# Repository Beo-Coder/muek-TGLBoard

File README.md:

# TGL Board

### 8x16 ARGB LED Board

This project is a small low profile PCB LED matrix that can be used as a name tag
or to display various text and animations and to play games.

If you have your own "programmable" version,
you can read more about programming [here](#programming)

# About
This project was initially planned as a gift for teachers after our graduation.  
It is a small and low cost LED matrix board.  
It consists of a 8x16 ARGB LED matrix, two buttons as user input and a USB-C jack for powering and programming. 
On the front and backside there are several places where custom text can be written to,
to further individualize the board.  
One of the main goals was that the whole board is visually appealing
and can be used without an enclosure to have a simpler and sleeker looking product.

The electronics consist of an RP2040 microcontroller and a 2 MB (16 Mbit) flash IC.  
You can read more about the electronic [here](#hardware)

To program the board,
you can use SWD on the Tag-Connect connector on the backside as well as on the [custom pads on the backside](#swd-interface).  
It is also possible to program the board over USB-C,
but this needs further hardware modifications (Read more about [here](#usb-c))

# Software
Currently, the software has four modes:

- Displaying text
- Showing animations
- Playing a game
- Setting the brightness

Between these modes, you can easily switch by holding down both buttons at the same time and waiting a bit.
You can choose the mode by going left or right and select it by either waiting or pressing both buttons again.

Inside the different modes, the two buttons have different meanings.
They change the text, the color of the text, the animation, or you can play the game.

## Text
The text can be individually programmed by modifying the [board_text_config.h](src/DisplayText/board_text_config.h) file.

## Animations
There are currently seven different animations:

- Fireworks
- Snake "AI"
- Conway's Game of Life
- Meteorite rain
- Smooth rainbow
- 'Hard' rainbow
- Jumping 'thing'

## Games
There are also two games, but only one is selected by default.

- Dino Game (Default)
- Tetris

To change the game, you need to modify [main.cpp](src/main.cpp).

### Controls: 
#### Dino Game: 
**Left**: *Duck*  
**Right**: *Jump*

After each game, your score and your high score is shown.

#### Tetris:
**Left**: *Moves block to the left*  
**Right**: *Moves block to the right*  
**Right while holding left**: *Rotating block*

After each game, your score and your high score is shown.  
This Tetris game was created by @StarMiner99

## Brightness control
The brightness is only saved when you switch the menu after setting the desired brightness.

# Programming
You can either use PlatformIO (Arduino Framework) or the official C/C++ SDK from Raspberry Pi.  
If you want to use the C/C++ SDK, please use the c-SDK branch.

For details on how these two differ, read [Runtime](README_runtime.md).

## Usage

You need PlatformIO to use this project.  
Arduino IDE might work too (not tested).

In the platform.ini file, there are now two build environments.
`pico_normal` and `pico_fast` you can read about the differences here [Runtime](README_runtime.md).  

For your own programming, you can use my pioMatrixOutput library.
Documentation is here [pioMatrixOutput](READMEpioMatrixOutput.md).

For your own text, you can use my library.
Documentation is here [Textcontroller](README_textController.md).

For flash usage, read here [Flash](README_flash.md).

**Important:**
If you brick your board (can't upload anything) please read [here](README_bricked.md).  

# Hardware

Schematic, layout, BOM and gerber files can be found [here](hardware).  

Each button has a 10k-ohm pull-down resistor and a 100-nF capacitor for debouncing.  

The design of the MCU section follows more or less the [hardware design guide for the RP2040](https://datasheets.raspberrypi.com/rp2040/hardware-design-with-rp2040.pdf).

Because of the design,
it was not possible to add a 100-nF capacitor to each LED, but each row of LEDs (16 each) has its own 10-uF cap
(I know it is not perfect or a replacement).  
Also,
there are multiple more capacitors to further decouple the matrix as good as possible
so that fast-changing patterns do not affect the MCU and its operations.  
This is further improved by the fact the whole MCU subsystem runs on 3.3V over a LDO and not the 5.0V that the LEDs run on. 
While testing, I haven't had any issues with noisy power lines.  
Also, when measuring with my oscilloscope and the matrix turning fully on and fully off as fast as possible, 
I couldn't measure any serious noise on the 5.0V rail nor on the 3.3V rail for the MCU.

## USB-C
Behind the USB-C jack, there are two unpopulated pads.
These pads cut the USB data signal, so that you can't program the board over USB.  
This can be useful, for example,
if you do not want that your teachers get confused when they plug it in to their pc :^)  
If you want to enable USB programming,
you need to short these two pads either with an 0402 0-ohm resistor or simply with solder bridges.  
Be aware that this is quite challenging to solder, you shouldn't destroy/desolder neighboring components.  
Maybe it is easier if you use a hotplate and 0-ohm resistors (Haven't tried it).  
If you order new boards, you can add those to be assembled too.  
The 27-ohm resistors on each USB data line necessary for the RP2040 are already assembled.

It should look something like this:

## SWD interface
The three unnamed pads on the backside above the UART pads are connections for SWD programming. 

Pinout:
<pre>
board outline
 |
 |          +---+            +---+           +---+
 |         /     \          /     \         /     \
 |        /       \        /       \       /       \
 |       +   RUN   +      +   SWD   +     +  SWCLK  +
 |        \       /        \       /       \       /
 |         \     /          \     /         \     /
 |          +---+            +---+           +---+
 |
 |                  +---+            +---+          
 |                 /     \          /     \ 
 |                /       \        /       \
 |               +   Tx    +      +   Rx    +
 |                \       /        \       /       
 |                 \     /          \     /   
 |                  +---+            +---+
</pre>

# Stand
I also created a stand for the board.
It has three different angles: 90°, 70° and 60°.  
It has place for a name on the top side and for text on the bottom side.  
Inside the stand there are three slots for 1 cent coins (EU) to make the stand more stable.  
If you want to insert those coins, you need to stop the print mid-way and insert/glue the coins in place.  
3mf and STL files can be found [here](hardware/Stand)

If you have any questions, please contact me.

© 2024 Leonhard Baschang

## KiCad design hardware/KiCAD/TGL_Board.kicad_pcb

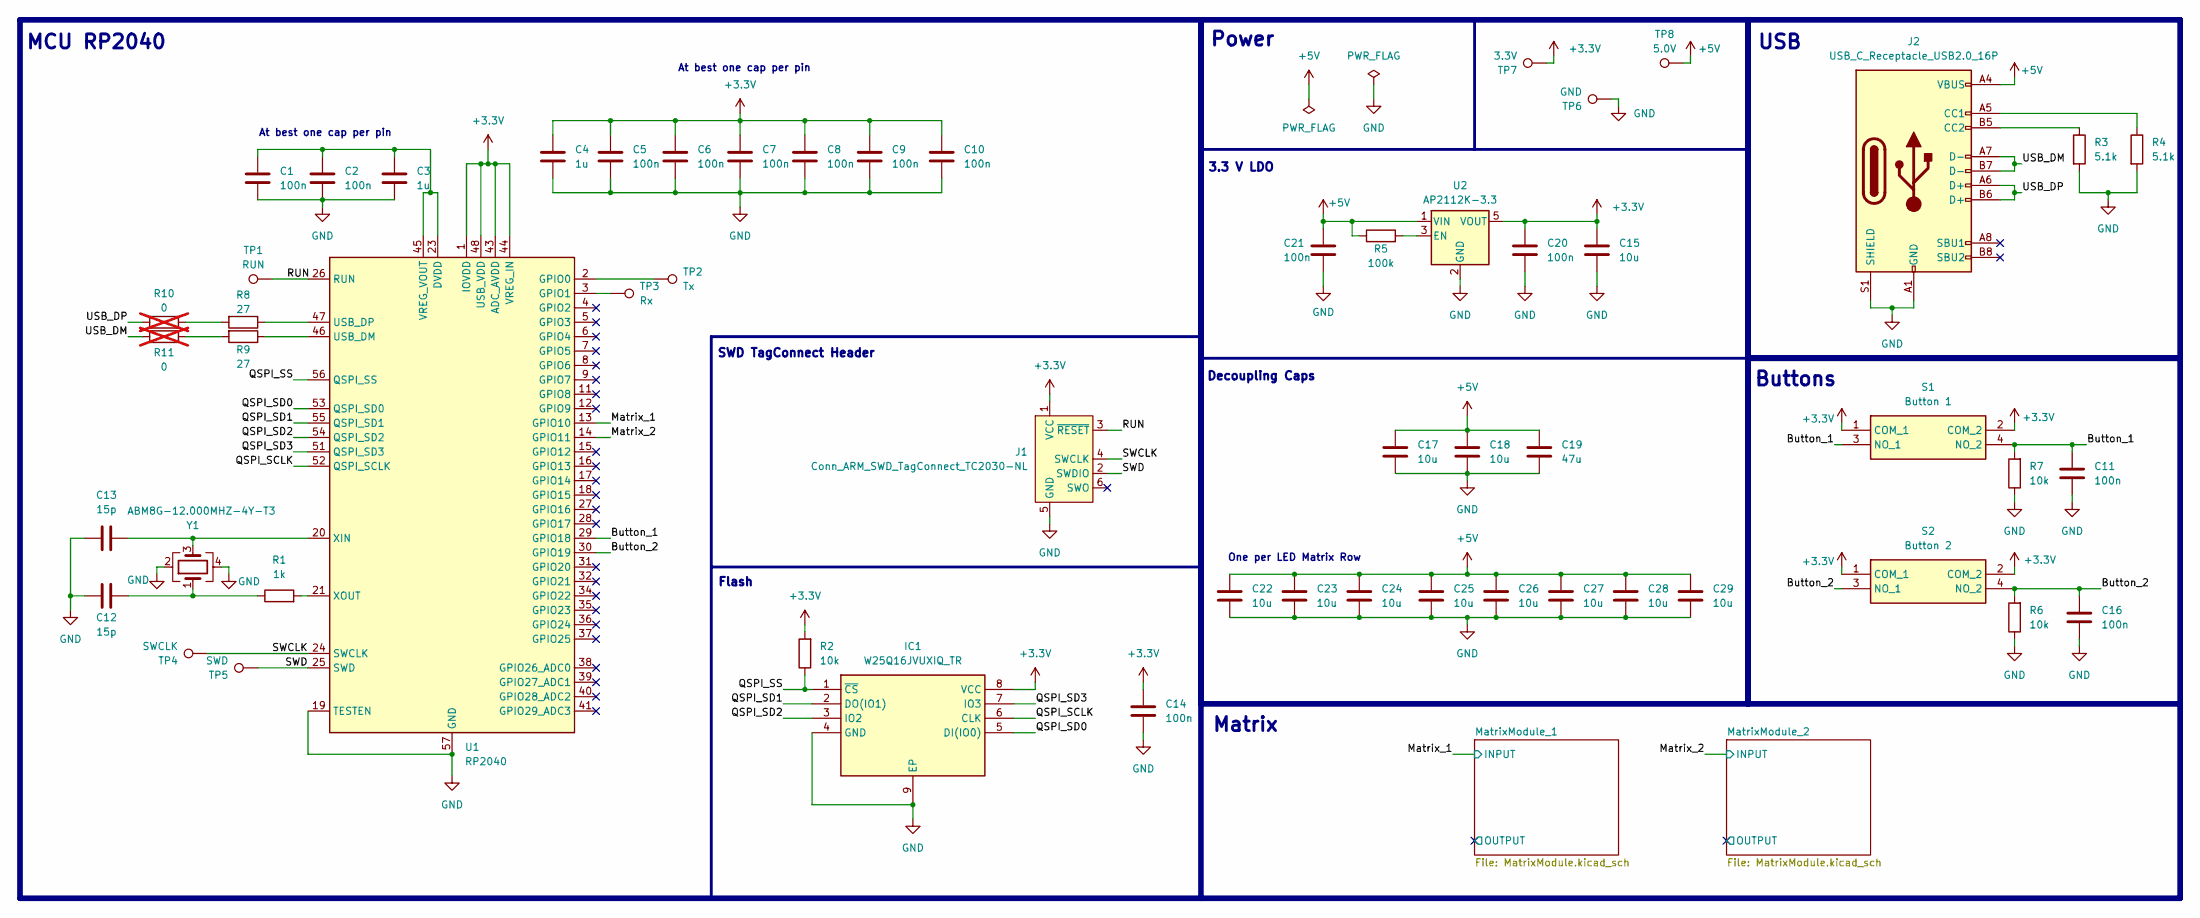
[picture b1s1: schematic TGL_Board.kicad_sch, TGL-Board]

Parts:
C1, C2, C5, C6, C7, C8, C9, C10, C11, C14, C16, C20, C21: 100n; C_0402_1005Metric; LCSC C1525
C3, C4: 1u; C_0402_1005Metric; LCSC C52923
C12, C13: 15p; C_0402_1005Metric; LCSC C1548
C15, C17, C18, C22, C23, C24, C25, C26, C27, C28, C29: 10u; C_0603_1608Metric; LCSC C19702
C19: 47u; C_0805_2012Metric; LCSC C16780
IC1: W25Q16JVUXIQ_TR; SON50P300X200X60-9L; Mouser Part Number 454-W25Q16JVUXIQTR
J1: Conn_ARM_SWD_TagConnect_TC2030-NL; Tag-Connect_TC2030-IDC-NL_2x03_P1.27mm_Vertical
J2: USB_C_Receptacle_USB2.0_16P; USB_C_Receptacle_GCT_USB4105-xx-A_16P_TopMnt_Horizontal; LCSC C2858270
R1: 1k; R_0402_1005Metric; LCSC C11702
R2, R6, R7: 10k; R_0402_1005Metric; LCSC C25744
R3, R4: 5.1k; R_0402_1005Metric; LCSC C25905
R5: 100k; R_0402_1005Metric; LCSC C25741
R8, R9: 27; R_0402_1005Metric; LCSC C25156
R10, R11: 0; R_0402_1005Metric; not fitted
S1: Button 1; PTS526SK15SMTR2LFS; Mouser Part Number 611-PTS526SK15SMR2L
S2: Button 2; PTS526SK15SMTR2LFS; Mouser Part Number 611-PTS526SK15SMR2L
TP1: RUN; TestPoint_Pad_D1.0mm
TP2: Tx; TestPoint_Pad_D1.0mm
TP3: Rx; TestPoint_Pad_D1.0mm
TP4: SWCLK; TestPoint_Pad_D1.0mm
TP5: SWD; TestPoint_Pad_D1.0mm
TP6: GND; TestPoint_Pad_D1.0mm
TP7: 3.3V; TestPoint_Pad_D1.0mm
TP8: 5.0V; TestPoint_Pad_D1.0mm
U1: RP2040; QFN-56-1EP_7x7mm_P0.4mm_EP3.2x3.2mm; LCSC C2040
U2: AP2112K-3.3; SOT-23-5; LCSC C51118
Y1: ABM8G-12.000MHZ-4Y-T3; Crystal_SMD_3225-4Pin_3.2x2.5mm; LCSC C9002

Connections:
+3.3V: C4.1, C5.2, C6.2, C7.2, C8.2, C9.2, C10.2, C14.1, C15.2, C20.2, IC1.8 (VCC), J1.1 (VCC), R2.2, S1.1 (COM_1), S1.2 (COM_2), S2.1 (COM_1), S2.2 (COM_2), TP7.1, U1.1 (IOVDD), U1.10 (IOVDD), U1.22 (IOVDD), U1.33 (IOVDD), U1.42 (IOVDD), U1.43 (ADC_AVDD), U1.44 (VREG_IN), U1.48 (USB_VDD), U1.49 (IOVDD), U2.5 (VOUT)
+5V: C17.2, C18.2, C19.2, C21.1, C22.2, C23.2, C24.2, C25.2, C26.2, C27.2, C28.2, C29.2, J2.A4 (VBUS), J2.A9 (VBUS), J2.B4 (VBUS), J2.B9 (VBUS), R5.1, TP8.1, U2.1 (VIN); also elsewhere on the board
/Button_1: C11.2, R7.2, S1.3 (NO_1), S1.4 (NO_2), U1.29 (GPIO18)
/Button_2: C16.2, R6.2, S2.3 (NO_1), S2.4 (NO_2), U1.30 (GPIO19)
/Matrix_1: U1.13 (GPIO10); also elsewhere on the board
/Matrix_2: U1.14 (GPIO11); also elsewhere on the board
/QSPI_SCLK: IC1.6 (CLK), U1.52 (QSPI_SCLK)
/QSPI_SD0: IC1.5 (DI(IO0)), U1.53 (QSPI_SD0)
/QSPI_SD1: IC1.2 (DO(IO1)), U1.55 (QSPI_SD1)
/QSPI_SD2: IC1.3 (IO2), U1.54 (QSPI_SD2)
/QSPI_SD3: IC1.7 (IO3), U1.51 (QSPI_SD3)
/QSPI_SS: IC1.1 (~CS), R2.1, U1.56 (QSPI_SS)
/RUN: J1.3 (~RESET), TP1.1, U1.26 (RUN)
/SWCLK: J1.4 (SWCLK), TP4.1, U1.24 (SWCLK)
/SWD: J1.2 (SWDIO), TP5.1, U1.25 (SWD)
/USB_DM: J2.A7 (D-), J2.B7 (D-), R11.2
/USB_DP: J2.A6 (D+), J2.B6 (D+), R10.2
GND: C1.1, C2.1, C3.1, C4.2, C5.1, C6.1, C7.1, C8.1, C9.1, C10.1, C11.1, C12.2, C13.2, C14.2, C15.1, C16.1, C17.1, C18.1, C19.1, C20.1, C21.2, C22.1, C23.1, C24.1, C25.1, C26.1, C27.1, C28.1, C29.1, IC1.4 (GND), IC1.9 (EP), J1.5 (GND), J2.A1 (GND), J2.A12 (GND), J2.B1 (GND), J2.B12 (GND), J2.S1 (SHIELD), R3.2, R4.2, R6.1, R7.1, TP6.1, U1.19 (TESTEN), U1.57 (GND), U2.2 (GND), Y1.2, Y1.4; also elsewhere on the board
unnamed: C12.1, R1.1, Y1.1
unnamed: J2.A5 (CC1), R4.1
unnamed: J2.B5 (CC2), R3.1
unnamed: R8.2, R10.1
unnamed: R9.2, R11.1
unnamed: TP2.1, U1.2 (GPIO0)
unnamed: TP3.1, U1.3 (GPIO1)
unnamed: R9.1, U1.46 (USB_DM)
unnamed: R8.1, U1.47 (USB_DP)
unnamed: C1.2, C2.2, C3.2, U1.23 (DVDD), U1.45 (VREG_VOUT), U1.50 (DVDD)
unnamed: C13.1, U1.20 (XIN), Y1.3
unnamed: R1.2, U1.21 (XOUT)
unnamed: R5.2, U2.3 (EN)

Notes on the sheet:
3.3 V LDO
USB
Matrix
At best one cap per pin
One per LED Matrix Row
Power
Flash
MCU RP2040
Decoupling Caps
SWD TagConnect Header
Buttons

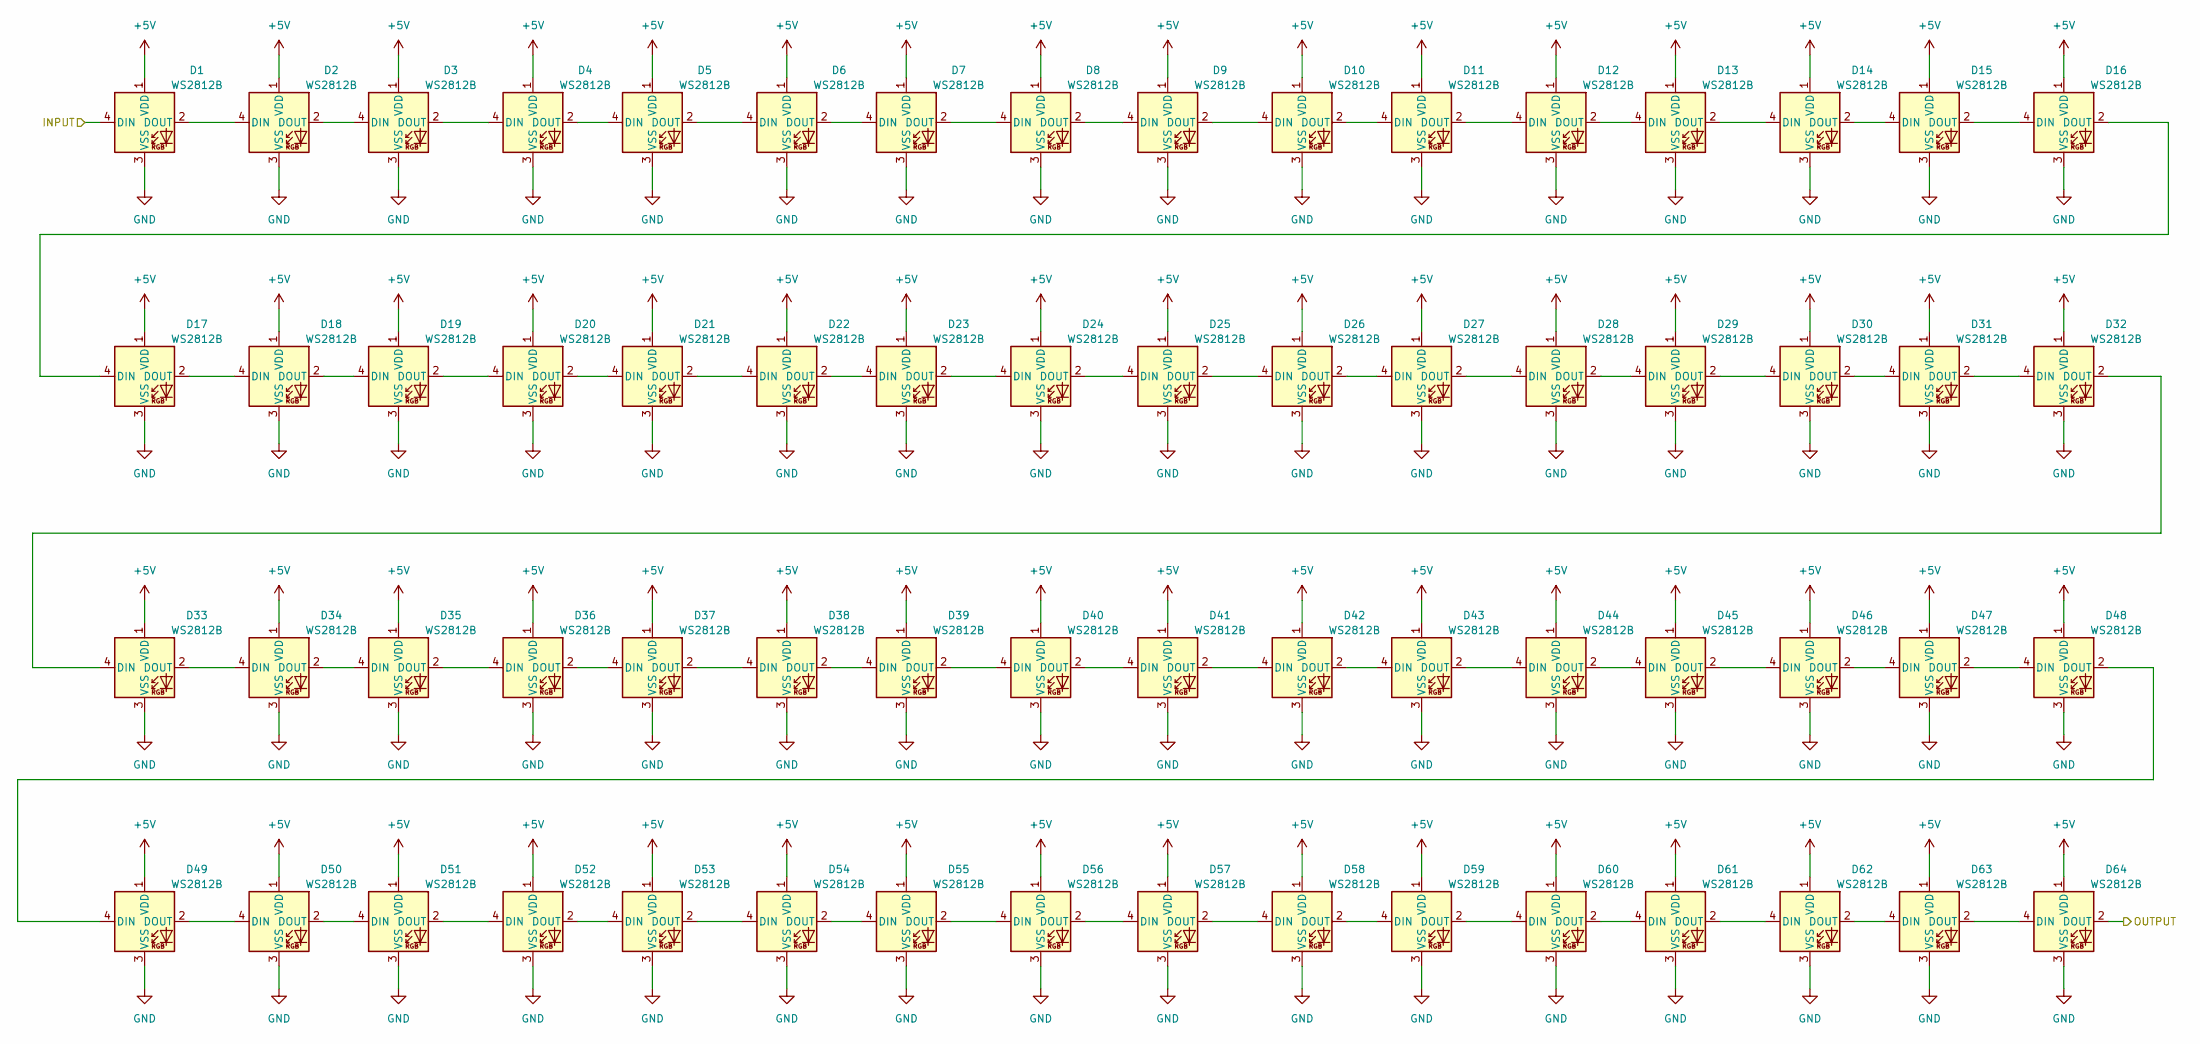
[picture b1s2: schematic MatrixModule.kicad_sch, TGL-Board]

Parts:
D1, D2, D3, D4, D5, D6, D7, D8, D9, D10, D11, D12, D13, D14, D15, D16, D17, D18, D19, D20, D21, D22, D23, D24, D25, D26, D27, D28, D29, D30, D31, D32, D33, D34, D35, D36, D37, D38, D39, D40, D41, D42, D43, D44, D45, D46, D47, D48, D49, D50, D51, D52, D53, D54, D55, D56, D57, D58, D59, D60, D61, D62, D63, D64: WS2812B; LED_WS2812B_XL-1615RGBC-WS2812B; LCSC C5349954

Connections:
+5V: D1.1 (VDD), D2.1 (VDD), D3.1 (VDD), D4.1 (VDD), D5.1 (VDD), D6.1 (VDD), D7.1 (VDD), D8.1 (VDD), D9.1 (VDD), D10.1 (VDD), D11.1 (VDD), D12.1 (VDD), D13.1 (VDD), D14.1 (VDD), D15.1 (VDD), D16.1 (VDD), D17.1 (VDD), D18.1 (VDD), D19.1 (VDD), D20.1 (VDD), D21.1 (VDD), D22.1 (VDD), D23.1 (VDD), D24.1 (VDD), D25.1 (VDD), D26.1 (VDD), D27.1 (VDD), D28.1 (VDD), D29.1 (VDD), D30.1 (VDD), D31.1 (VDD), D32.1 (VDD), D33.1 (VDD), D34.1 (VDD), D35.1 (VDD), D36.1 (VDD), D37.1 (VDD), D38.1 (VDD), D39.1 (VDD), D40.1 (VDD), D41.1 (VDD), D42.1 (VDD), D43.1 (VDD), D44.1 (VDD), D45.1 (VDD), D46.1 (VDD), D47.1 (VDD), D48.1 (VDD), D49.1 (VDD), D50.1 (VDD), D51.1 (VDD), D52.1 (VDD), D53.1 (VDD), D54.1 (VDD), D55.1 (VDD), D56.1 (VDD), D57.1 (VDD), D58.1 (VDD), D59.1 (VDD), D60.1 (VDD), D61.1 (VDD), D62.1 (VDD), D63.1 (VDD), D64.1 (VDD); also elsewhere on the board
/MatrixModule_1/OUTPUT: D64.2 (DOUT)
/Matrix_1: D1.4 (DIN); also elsewhere on the board
GND: D1.3 (VSS), D2.3 (VSS), D3.3 (VSS), D4.3 (VSS), D5.3 (VSS), D6.3 (VSS), D7.3 (VSS), D8.3 (VSS), D9.3 (VSS), D10.3 (VSS), D11.3 (VSS), D12.3 (VSS), D13.3 (VSS), D14.3 (VSS), D15.3 (VSS), D16.3 (VSS), D17.3 (VSS), D18.3 (VSS), D19.3 (VSS), D20.3 (VSS), D21.3 (VSS), D22.3 (VSS), D23.3 (VSS), D24.3 (VSS), D25.3 (VSS), D26.3 (VSS), D27.3 (VSS), D28.3 (VSS), D29.3 (VSS), D30.3 (VSS), D31.3 (VSS), D32.3 (VSS), D33.3 (VSS), D34.3 (VSS), D35.3 (VSS), D36.3 (VSS), D37.3 (VSS), D38.3 (VSS), D39.3 (VSS), D40.3 (VSS), D41.3 (VSS), D42.3 (VSS), D43.3 (VSS), D44.3 (VSS), D45.3 (VSS), D46.3 (VSS), D47.3 (VSS), D48.3 (VSS), D49.3 (VSS), D50.3 (VSS), D51.3 (VSS), D52.3 (VSS), D53.3 (VSS), D54.3 (VSS), D55.3 (VSS), D56.3 (VSS), D57.3 (VSS), D58.3 (VSS), D59.3 (VSS), D60.3 (VSS), D61.3 (VSS), D62.3 (VSS), D63.3 (VSS), D64.3 (VSS); also elsewhere on the board
unnamed: D1.2 (DOUT), D2.4 (DIN)
unnamed: D2.2 (DOUT), D3.4 (DIN)
unnamed: D3.2 (DOUT), D4.4 (DIN)
unnamed: D4.2 (DOUT), D5.4 (DIN)
unnamed: D5.2 (DOUT), D6.4 (DIN)
unnamed: D6.2 (DOUT), D7.4 (DIN)
unnamed: D7.2 (DOUT), D8.4 (DIN)
unnamed: D8.2 (DOUT), D9.4 (DIN)
unnamed: D9.2 (DOUT), D10.4 (DIN)
unnamed: D10.2 (DOUT), D11.4 (DIN)
unnamed: D11.2 (DOUT), D12.4 (DIN)
unnamed: D12.2 (DOUT), D13.4 (DIN)
unnamed: D13.2 (DOUT), D14.4 (DIN)
unnamed: D14.2 (DOUT), D15.4 (DIN)
unnamed: D15.2 (DOUT), D16.4 (DIN)
unnamed: D16.2 (DOUT), D17.4 (DIN)
unnamed: D17.2 (DOUT), D18.4 (DIN)
unnamed: D18.2 (DOUT), D19.4 (DIN)
unnamed: D19.2 (DOUT), D20.4 (DIN)
unnamed: D20.2 (DOUT), D21.4 (DIN)
unnamed: D21.2 (DOUT), D22.4 (DIN)
unnamed: D22.2 (DOUT), D23.4 (DIN)
unnamed: D23.2 (DOUT), D24.4 (DIN)
unnamed: D24.2 (DOUT), D25.4 (DIN)
unnamed: D25.2 (DOUT), D26.4 (DIN)
unnamed: D26.2 (DOUT), D27.4 (DIN)
unnamed: D27.2 (DOUT), D28.4 (DIN)
unnamed: D28.2 (DOUT), D29.4 (DIN)
unnamed: D29.2 (DOUT), D30.4 (DIN)
unnamed: D30.2 (DOUT), D31.4 (DIN)
unnamed: D31.2 (DOUT), D32.4 (DIN)
unnamed: D32.2 (DOUT), D33.4 (DIN)
unnamed: D33.2 (DOUT), D34.4 (DIN)
unnamed: D34.2 (DOUT), D35.4 (DIN)
unnamed: D35.2 (DOUT), D36.4 (DIN)
unnamed: D36.2 (DOUT), D37.4 (DIN)
unnamed: D37.2 (DOUT), D38.4 (DIN)
unnamed: D38.2 (DOUT), D39.4 (DIN)
unnamed: D39.2 (DOUT), D40.4 (DIN)
unnamed: D40.2 (DOUT), D41.4 (DIN)
unnamed: D41.2 (DOUT), D42.4 (DIN)
unnamed: D42.2 (DOUT), D43.4 (DIN)
unnamed: D43.2 (DOUT), D44.4 (DIN)
unnamed: D44.2 (DOUT), D45.4 (DIN)
unnamed: D45.2 (DOUT), D46.4 (DIN)
unnamed: D46.2 (DOUT), D47.4 (DIN)
unnamed: D47.2 (DOUT), D48.4 (DIN)
unnamed: D48.2 (DOUT), D49.4 (DIN)
unnamed: D49.2 (DOUT), D50.4 (DIN)
unnamed: D50.2 (DOUT), D51.4 (DIN)
unnamed: D51.2 (DOUT), D52.4 (DIN)
unnamed: D52.2 (DOUT), D53.4 (DIN)
unnamed: D53.2 (DOUT), D54.4 (DIN)
unnamed: D54.2 (DOUT), D55.4 (DIN)
unnamed: D55.2 (DOUT), D56.4 (DIN)
unnamed: D56.2 (DOUT), D57.4 (DIN)
unnamed: D57.2 (DOUT), D58.4 (DIN)
unnamed: D58.2 (DOUT), D59.4 (DIN)
unnamed: D59.2 (DOUT), D60.4 (DIN)
unnamed: D60.2 (DOUT), D61.4 (DIN)
unnamed: D61.2 (DOUT), D62.4 (DIN)
unnamed: D62.2 (DOUT), D63.4 (DIN)
unnamed: D63.2 (DOUT), D64.4 (DIN)

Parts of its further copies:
D65, D66, D67, D68, D69, D70, D71, D72, D73, D74, D75, D76, D77, D78, D79, D80, D81, D82, D83, D84, D85, D86, D87, D88, D89, D90, D91, D92, D93, D94, D95, D96, D97, D98, D99, D100, D101, D102, D103, D104, D105, D106, D107, D108, D109, D110, D111, D112, D113, D114, D115, D116, D117, D118, D119, D120, D121, D122, D123, D124, D125, D126, D127, D128: WS2812B; LED_WS2812B_XL-1615RGBC-WS2812B; LCSC C5349954

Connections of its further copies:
+5V: D65.1 (VDD), D66.1 (VDD), D67.1 (VDD), D68.1 (VDD), D69.1 (VDD), D70.1 (VDD), D71.1 (VDD), D72.1 (VDD), D73.1 (VDD), D74.1 (VDD), D75.1 (VDD), D76.1 (VDD), D77.1 (VDD), D78.1 (VDD), D79.1 (VDD), D80.1 (VDD), D81.1 (VDD), D82.1 (VDD), D83.1 (VDD), D84.1 (VDD), D85.1 (VDD), D86.1 (VDD), D87.1 (VDD), D88.1 (VDD), D89.1 (VDD), D90.1 (VDD), D91.1 (VDD), D92.1 (VDD), D93.1 (VDD), D94.1 (VDD), D95.1 (VDD), D96.1 (VDD), D97.1 (VDD), D98.1 (VDD), D99.1 (VDD), D100.1 (VDD), D101.1 (VDD), D102.1 (VDD), D103.1 (VDD), D104.1 (VDD), D105.1 (VDD), D106.1 (VDD), D107.1 (VDD), D108.1 (VDD), D109.1 (VDD), D110.1 (VDD), D111.1 (VDD), D112.1 (VDD), D113.1 (VDD), D114.1 (VDD), D115.1 (VDD), D116.1 (VDD), D117.1 (VDD), D118.1 (VDD), D119.1 (VDD), D120.1 (VDD), D121.1 (VDD), D122.1 (VDD), D123.1 (VDD), D124.1 (VDD), D125.1 (VDD), D126.1 (VDD), D127.1 (VDD), D128.1 (VDD); also elsewhere on the board
/MatrixModule_2/OUTPUT: D128.2 (DOUT)
/Matrix_2: D65.4 (DIN); also elsewhere on the board
GND: D65.3 (VSS), D66.3 (VSS), D67.3 (VSS), D68.3 (VSS), D69.3 (VSS), D70.3 (VSS), D71.3 (VSS), D72.3 (VSS), D73.3 (VSS), D74.3 (VSS), D75.3 (VSS), D76.3 (VSS), D77.3 (VSS), D78.3 (VSS), D79.3 (VSS), D80.3 (VSS), D81.3 (VSS), D82.3 (VSS), D83.3 (VSS), D84.3 (VSS), D85.3 (VSS), D86.3 (VSS), D87.3 (VSS), D88.3 (VSS), D89.3 (VSS), D90.3 (VSS), D91.3 (VSS), D92.3 (VSS), D93.3 (VSS), D94.3 (VSS), D95.3 (VSS), D96.3 (VSS), D97.3 (VSS), D98.3 (VSS), D99.3 (VSS), D100.3 (VSS), D101.3 (VSS), D102.3 (VSS), D103.3 (VSS), D104.3 (VSS), D105.3 (VSS), D106.3 (VSS), D107.3 (VSS), D108.3 (VSS), D109.3 (VSS), D110.3 (VSS), D111.3 (VSS), D112.3 (VSS), D113.3 (VSS), D114.3 (VSS), D115.3 (VSS), D116.3 (VSS), D117.3 (VSS), D118.3 (VSS), D119.3 (VSS), D120.3 (VSS), D121.3 (VSS), D122.3 (VSS), D123.3 (VSS), D124.3 (VSS), D125.3 (VSS), D126.3 (VSS), D127.3 (VSS), D128.3 (VSS); also elsewhere on the board
unnamed: D65.2 (DOUT), D66.4 (DIN)
unnamed: D66.2 (DOUT), D67.4 (DIN)
unnamed: D67.2 (DOUT), D68.4 (DIN)
unnamed: D68.2 (DOUT), D69.4 (DIN)
unnamed: D69.2 (DOUT), D70.4 (DIN)
unnamed: D70.2 (DOUT), D71.4 (DIN)
unnamed: D71.2 (DOUT), D72.4 (DIN)
unnamed: D72.2 (DOUT), D73.4 (DIN)
unnamed: D73.2 (DOUT), D74.4 (DIN)
unnamed: D74.2 (DOUT), D75.4 (DIN)
unnamed: D75.2 (DOUT), D76.4 (DIN)
unnamed: D76.2 (DOUT), D77.4 (DIN)
unnamed: D77.2 (DOUT), D78.4 (DIN)
unnamed: D78.2 (DOUT), D79.4 (DIN)
unnamed: D79.2 (DOUT), D80.4 (DIN)
unnamed: D80.2 (DOUT), D81.4 (DIN)
unnamed: D81.2 (DOUT), D82.4 (DIN)
unnamed: D82.2 (DOUT), D83.4 (DIN)
unnamed: D83.2 (DOUT), D84.4 (DIN)
unnamed: D84.2 (DOUT), D85.4 (DIN)
unnamed: D85.2 (DOUT), D86.4 (DIN)
unnamed: D86.2 (DOUT), D87.4 (DIN)
unnamed: D87.2 (DOUT), D88.4 (DIN)
unnamed: D88.2 (DOUT), D89.4 (DIN)
unnamed: D89.2 (DOUT), D90.4 (DIN)
unnamed: D90.2 (DOUT), D91.4 (DIN)
unnamed: D91.2 (DOUT), D92.4 (DIN)
unnamed: D92.2 (DOUT), D93.4 (DIN)
unnamed: D93.2 (DOUT), D94.4 (DIN)
unnamed: D94.2 (DOUT), D95.4 (DIN)
unnamed: D95.2 (DOUT), D96.4 (DIN)
unnamed: D96.2 (DOUT), D97.4 (DIN)
unnamed: D97.2 (DOUT), D98.4 (DIN)
unnamed: D98.2 (DOUT), D99.4 (DIN)
unnamed: D99.2 (DOUT), D100.4 (DIN)
unnamed: D100.2 (DOUT), D101.4 (DIN)
unnamed: D101.2 (DOUT), D102.4 (DIN)
unnamed: D102.2 (DOUT), D103.4 (DIN)
unnamed: D103.2 (DOUT), D104.4 (DIN)
unnamed: D104.2 (DOUT), D105.4 (DIN)
unnamed: D105.2 (DOUT), D106.4 (DIN)
unnamed: D106.2 (DOUT), D107.4 (DIN)
unnamed: D107.2 (DOUT), D108.4 (DIN)
unnamed: D108.2 (DOUT), D109.4 (DIN)
unnamed: D109.2 (DOUT), D110.4 (DIN)
unnamed: D110.2 (DOUT), D111.4 (DIN)
unnamed: D111.2 (DOUT), D112.4 (DIN)
unnamed: D112.2 (DOUT), D113.4 (DIN)
unnamed: D113.2 (DOUT), D114.4 (DIN)
unnamed: D114.2 (DOUT), D115.4 (DIN)
unnamed: D115.2 (DOUT), D116.4 (DIN)
unnamed: D116.2 (DOUT), D117.4 (DIN)
unnamed: D117.2 (DOUT), D118.4 (DIN)
unnamed: D118.2 (DOUT), D119.4 (DIN)
unnamed: D119.2 (DOUT), D120.4 (DIN)
unnamed: D120.2 (DOUT), D121.4 (DIN)
unnamed: D121.2 (DOUT), D122.4 (DIN)
unnamed: D122.2 (DOUT), D123.4 (DIN)
unnamed: D123.2 (DOUT), D124.4 (DIN)
unnamed: D124.2 (DOUT), D125.4 (DIN)
unnamed: D125.2 (DOUT), D126.4 (DIN)
unnamed: D126.2 (DOUT), D127.4 (DIN)
unnamed: D127.2 (DOUT), D128.4 (DIN)

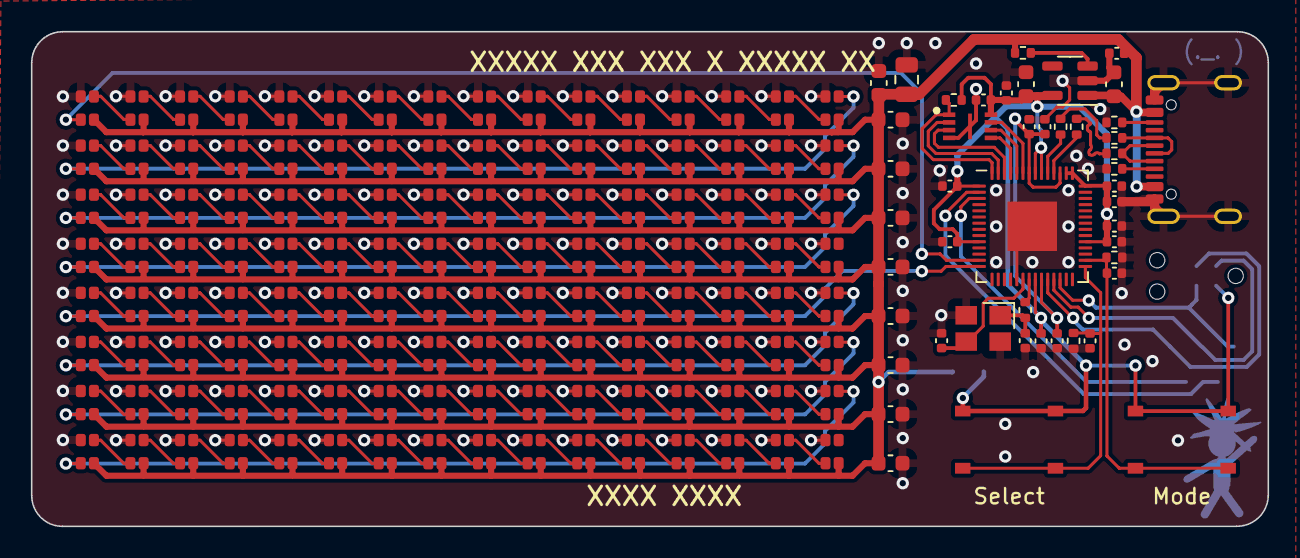
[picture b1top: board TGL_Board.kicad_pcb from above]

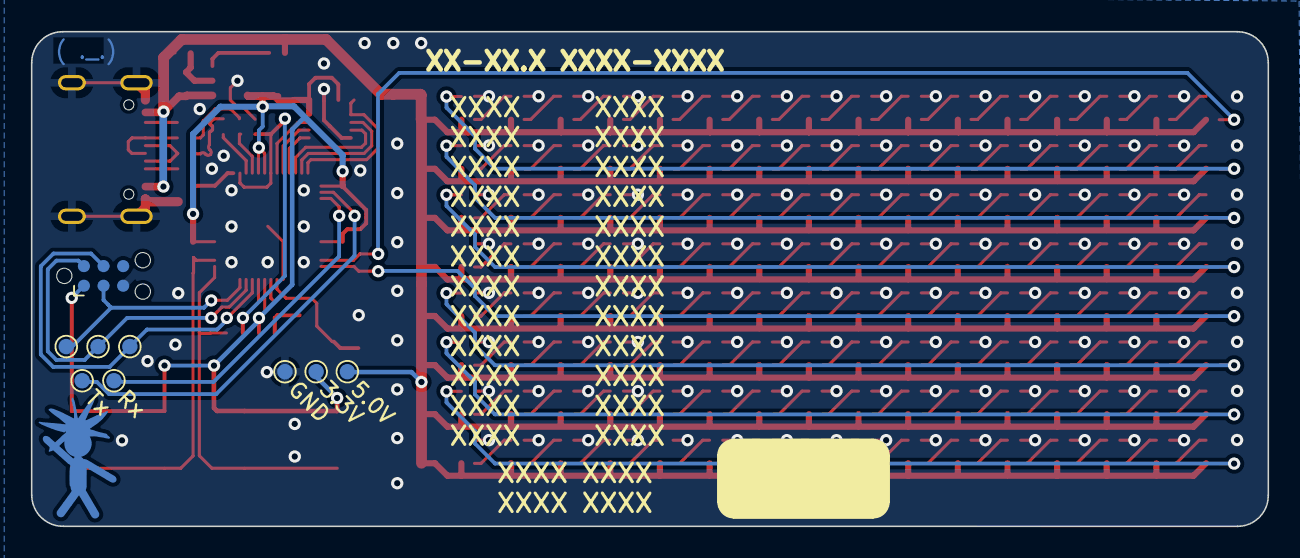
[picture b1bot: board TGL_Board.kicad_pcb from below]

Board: 2 copper layers, 80.0 x 32.0 mm, 184 parts (9 on the bottom side), 157 nets.

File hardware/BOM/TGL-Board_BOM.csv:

Reference,Value,Footprint,LCSC
"C1,C2,C5,C6,C7,C8,C9,C10,C11,C14,C16,C20,C21",100n,Capacitor_SMD:C_0402_1005Metric,C1525
"C3,C4",1u,Capacitor_SMD:C_0402_1005Metric,C52923
"C12,C13",15p,Capacitor_SMD:C_0402_1005Metric,C1548
"C15,C17,C18,C22,C23,C24,C25,C26,C27,C28,C29",10u,Capacitor_SMD:C_0603_1608Metric,C19702
C19,47u,Capacitor_SMD:C_0805_2012Metric,C16780
"D1,D2,D3,D4,D5,D6,D7,D8,D9,D10,D11,D12,D13,D14,D15,D16,D17,D18,D19,D20,D21,D22,D23,D24,D25,D26,D27,D28,D29,D30,D31,D32,D33,D34,D35,D36,D37,D38,D39,D40,D41,D42,D43,D44,D45,D46,D47,D48,D49,D50,D51,D52,D53,D54,D55,D56,D57,D58,D59,D60,D61,D62,D63,D64,D65,D66,D67,D68,D69,D70,D71,D72,D73,D74,D75,D76,D77,D78,D79,D80,D81,D82,D83,D84,D85,D86,D87,D88,D89,D90,D91,D92,D93,D94,D95,D96,D97,D98,D99,D100,D101,D102,D103,D104,D105,D106,D107,D108,D109,D110,D111,D112,D113,D114,D115,D116,D117,D118,D119,D120,D121,D122,D123,D124,D125,D126,D127,D128",WS2812B,LeosLib:LED_WS2812B_XL-1615RGBC-WS2812B,C5349954
IC1,W25Q16JVUXIQ_TR,W25Q16JVUXIQ:SON50P300X200X60-9L,C2843335
J2,USB_C_Receptacle_USB2.0_16P,Connector_USB:USB_C_Receptacle_GCT_USB4105-xx-A_16P_TopMnt_Horizontal,C2858270
R1,1k,Resistor_SMD:R_0402_1005Metric,C11702
"R2,R6,R7",10k,Resistor_SMD:R_0402_1005Metric,C25744
"R3,R4",5.1k,Resistor_SMD:R_0402_1005Metric,C25905
R5,100k,Resistor_SMD:R_0402_1005Metric,C25741
"R8,R9",27,Resistor_SMD:R_0402_1005Metric,C25156
S1,Button 1,PTS526:PTS526SK15SMTR2LFS,C318884
S2,Button 2,PTS526:PTS526SK15SMTR2LFS,C318884
U1,RP2040,Package_DFN_QFN:QFN-56-1EP_7x7mm_P0.4mm_EP3.2x3.2mm,C2040
U2,AP2112K-3.3,Package_TO_SOT_SMD:SOT-23-5,C51118
Y1,ABM8G-12.000MHZ-4Y-T3,Crystal:Crystal_SMD_3225-4Pin_3.2x2.5mm,C9002
,,,
,,,
,,,
,,,
,,,
,,,
,,,
,,,
,,,

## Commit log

2024-03-03 Initial commit Basic Output with PIO
2024-03-03 added letters.h
2024-04-23 Huge update (Frame Buffer, Subframes, ScrollText, ...)
2024-04-24 Added README.md and READMEpioMatrixOutput.md
2024-04-26 Added Dino game. Fixing color mess later :)
2024-04-26 Fixed some things
2024-04-28 added FireworkAnimation and my own random function
2024-04-28 added display_program class as superclass
2024-04-28 reworked scrollText and dinoGame to work with display_program
2024-04-28 renamed namespace
2024-04-28 Reworked dinoGame
2024-04-29 Reworked scrollText. Added more letters and added support for special chars
2024-04-29 Added static frame -> Less RAM usage
2024-04-30 Added more color options (brightness) Fireworks now explode Made a few changes to the output Controller (no more flickering pixels)
2024-04-30 Fireworks now copy their color instead of modifying the global one
2024-04-30 Fixed bug in firework
2024-05-01 Added start of a snake AI. Made randomInt more random using ROSC
2024-05-01 Renamed a bunch. Reorganized everything
2024-05-06 Changed a lot about the snake AI. I will change the hamiltonian circle algorithmen
2024-05-06 removed snakeAi from master for now
2024-05-06 fixed bug in framebuffer.cpp
2024-05-06 Added examples
2024-05-06 modified README.md
2024-05-06 Fixed typo
2024-05-06 Added scrollText Example and README for scrollText
2024-05-06 Added notes to READMEpioMatrixOutput.md
2024-05-06 Fixed READMEscrollText.md
2024-05-07 fixed typo for T.
2024-05-08 fixed some bugs/shit code
2024-05-08 Added pcb files
2024-05-08 wording
2024-05-09 added tetris classes
2024-05-09 added additional color methods
2024-05-09 made tetris inherit from display_program
2024-05-09 implemented tetris in main
2024-05-09 more subframes for .125 colors
2024-05-09 Added snakeAI
2024-05-09 Renamed SnakeAI
2024-05-09 changed pieces to static const
2024-05-09 use already existing frame instead of creating own
2024-05-09 removed redundancy
2024-05-09 splitted method out of code to make it more clean
2024-05-09 removed overlayMap to save on memory
2024-05-09 changed colorMap to pointer array to save on storage
2024-05-11 wrong array access fixed
2024-05-11 added score display
2024-05-11 Added support for C/C++ SDK. Changing the scrollText later wo work with other chars
2024-05-11 added update method so we can shift BEFORE we actually display it
2024-05-11 added scroll if needed
2024-05-11 changed shift condition
2024-05-11 Added a static-text ability to scroll text
2024-05-11 Changed scroll and static text. More changed incoming
2024-05-14 modified scroll text and static text
2024-05-14 Modified tetris to work with new static text controller. Fixed bug in static text controller
2024-05-17 Made static-text smarter and removed clearFrame from setText
2024-05-17 Fixed some stuff
2024-05-17 Added tiny text controller and reworked all text controllers
2024-05-18 Fixed imports and changed location of color
2024-05-18 Changed include guards
2024-05-18 Removed arduino specific code and added support for Pico C-SDK
2024-05-18 Changed README and examples
2024-05-18 Fixed some stuff for C-SDK
2024-05-18 Ups... Forgot something
2024-05-18 Renamed a file
2024-05-18 Renamed a file
    (cherry picked from commit 8a7585fc5a16ce9628e5541b531a54d07f3bc695)
2024-05-18 Renamed DisplayProgram
2024-05-19 fixed some timing issues
2024-05-19 added some buffer for timing
2024-05-19 Added game of life animation
2024-05-19 Added game of life
2024-05-20 Added support for better floating point computation
2024-05-22 Rework of color. Drastically improved divide operations and memory usage.
2024-05-22 fixed color multiply
2024-05-22 Modified things for C-SDK
2024-05-22 The Snake now fades at the end
2024-05-22 Game of Life now starts with a different color each "generation"
2024-05-22 Fixed some text controller single space things
2024-05-22 Fixed "Bug"/Added functionality
2024-05-22 Added score to Dino Game
2024-05-22 reset methode modified
2024-05-23 Added flash controller
2024-05-25 Fixed somethings in flash controller
2024-05-25 Fixed flash controller
2024-05-25 Added high score to dinoGame and tetris
2024-05-25 Added fixed animation
2024-05-25 Added rainbow animation
2024-05-25 Should have fixed bug that caused a crash after UIN32_T_MAX microseconds (~1 hour 11 minutes)
2024-05-26 Reduced flash consumption by jump animation
2024-05-26 Fixed issue in jump animation
2024-05-26 Added switcher menu
2024-05-26 better reset handling
2024-05-26 fixed jump start by dino game
2024-05-26 Fixed jump animation
2024-05-26 Set setText to const std::string
2024-05-26 Also set setColor to const
2024-05-26 Added displayText
2024-05-26 Added brightness control
2024-05-27 Set Platform IO framework version
2024-05-27 Text now switches on falling edge
2024-05-27 Better menu names
2024-05-27 Better refreshSpeed Dino Game
2024-05-27 Shorter long press hold time in menu
2024-06-11 Added exit function to display_program Brightness now gets stored
2024-06-11 Fixed flashbang start
2024-06-11 Better exit call
2024-06-11 Fixed some bugs and clean up
2024-06-13 Added meteorite animation
2024-06-13 Added second rainbow mode
2024-06-13 better const definition/initialization
2024-06-14 Added watchdog timer
2024-06-15 Better config for Display Text
2024-06-15 better snake ai moves
2024-06-15 better snake ai const and end
2024-06-15 typo
2024-06-19 Change back to old "AI" code
2024-06-26 Better letters
2024-06-26 Added .gitignore
2024-06-26 New board_text_config.h
2024-07-02 beo millis
2024-07-02 inline color
2024-07-02 added more colors
2024-07-03 better refresh speed and constant settings
2024-07-03 fixed bug in fireworks with overlaying fireworks
2024-07-03 fixed comments
2024-07-04 more and better README
2024-07-04 Fixed flash controller and some typos
2024-07-04 better code
2024-07-04 removed unnecessary code
2024-07-04 last minute bug fixing ( ._.)
2024-07-04 Late commit = good commit
2024-07-05 Added Copyright
2024-07-05 Another PI constant
